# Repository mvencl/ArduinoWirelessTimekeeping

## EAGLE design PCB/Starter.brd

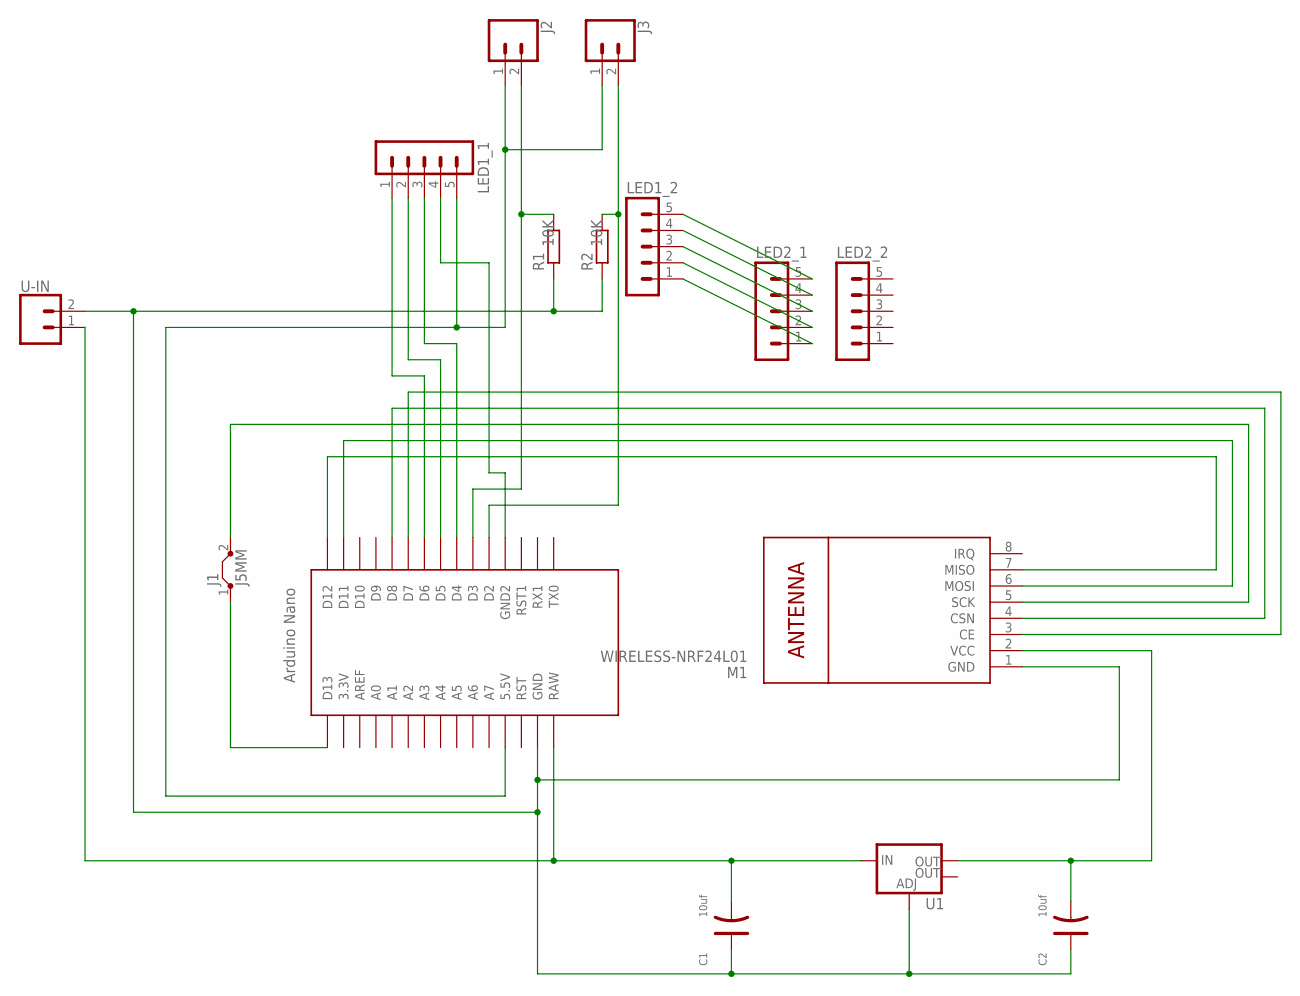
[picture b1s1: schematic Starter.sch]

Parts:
C1, C2: 10uf; AVX-B
J1: J5MM; 05
J2, J3: CONN_025MM; SCREWTERMINAL-5MM-2
LED1_1, LED1_2, LED2_1, LED2_2: MA05-1
M1: WIRELESS-NRF24L01
R1, R2: R-EU_0207/12; 0207/12
U1: V_REG_LM1117SOT223; SOT223
U$1: NANO
U-IN: CONN_025MM; SCREWTERMINAL-5MM-2

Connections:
unnamed: M1.4 (CSN), U$1.D8
unnamed: C1.+, C2.+, M1.1 (GND), R1.1, R2.1, U1.1 (ADJ), U$1.GND, U-IN.2
unnamed: C2.-, M1.2 (VCC), U1.2 (OUT)
unnamed: J1.2, M1.5 (SCK)
unnamed: LED1_2.5, LED2_1.5
unnamed: LED1_2.4, LED2_1.4
unnamed: LED1_2.3, LED2_1.3
unnamed: LED1_2.2, LED2_1.2
unnamed: LED1_2.1, LED2_1.1
unnamed: J2.1, J3.1, LED1_1.5, U$1.5V (5.5V)
unnamed: C1.-, U1.3 (IN), U$1.RAW, U-IN.1
unnamed: LED1_1.3, U$1.D4
unnamed: LED1_1.2, U$1.D5
unnamed: LED1_1.1, U$1.D6
unnamed: M1.3 (CE), U$1.D7
unnamed: M1.6 (MOSI), U$1.D11
unnamed: M1.7 (MISO), U$1.D12
unnamed: J2.2, R1.2, U$1.D3
unnamed: J3.2, R2.2, U$1.D2
unnamed: LED1_1.4, U$1.GND1 (GND2)
unnamed: J1.1, U$1.D13

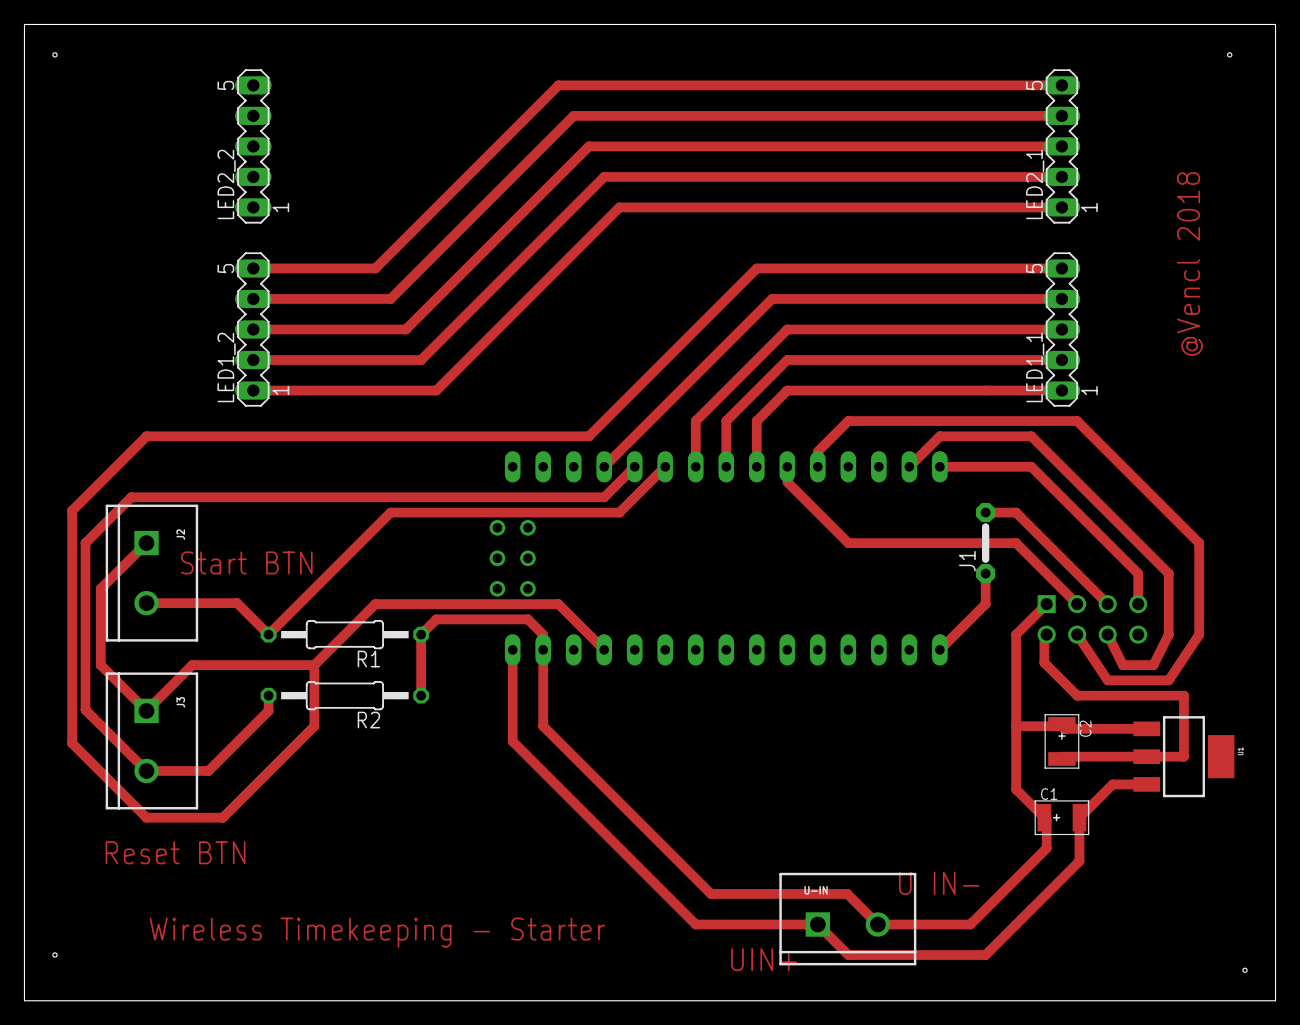
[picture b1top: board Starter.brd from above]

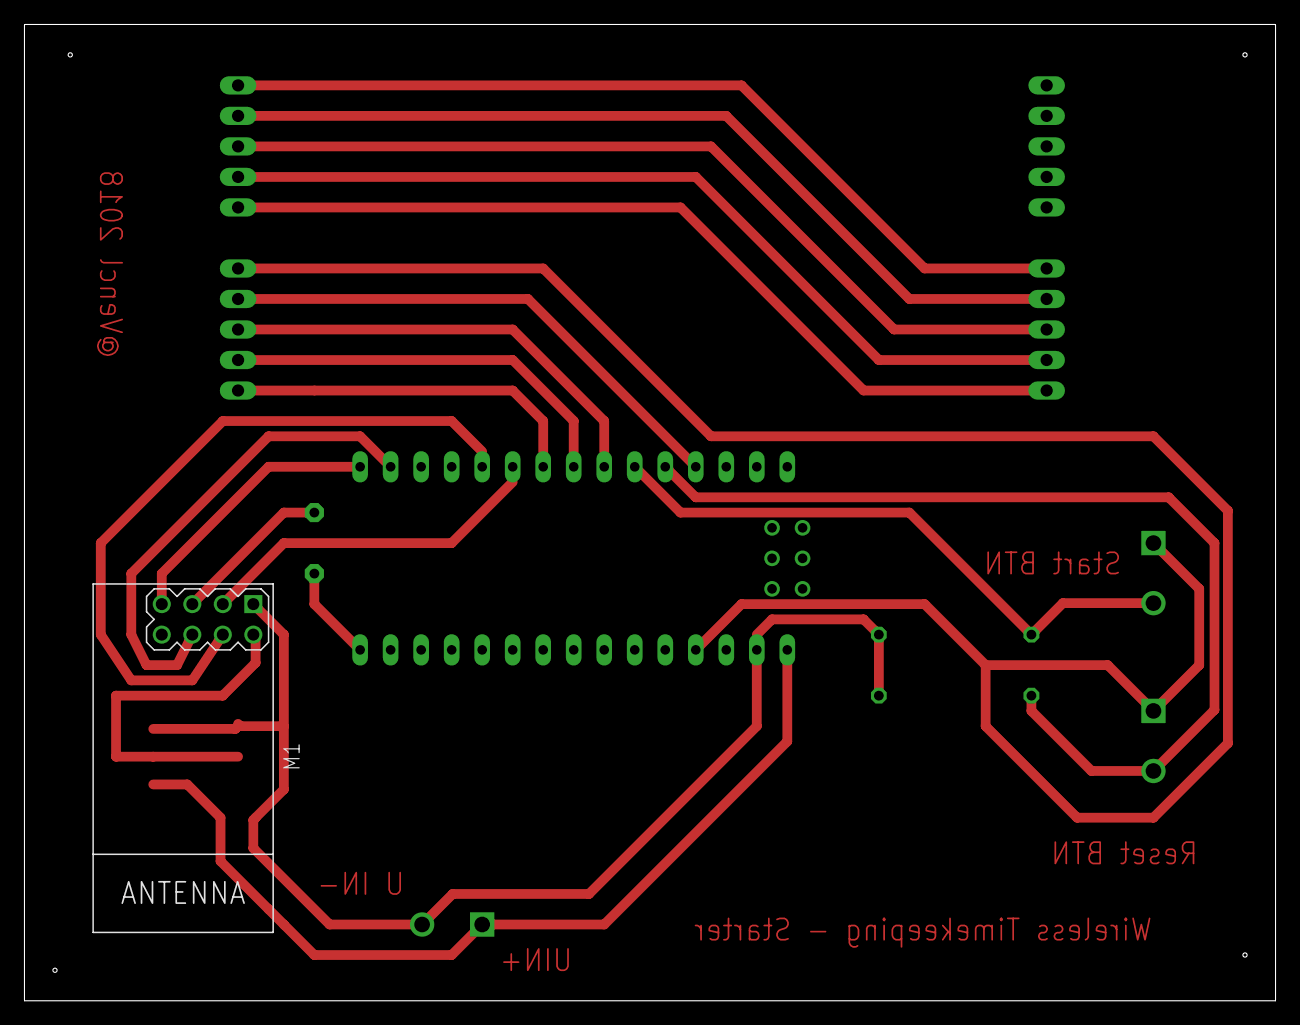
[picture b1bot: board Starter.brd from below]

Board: 2 copper layers, 104.1 x 81.3 mm, 15 parts (2 on the bottom side), 21 nets.

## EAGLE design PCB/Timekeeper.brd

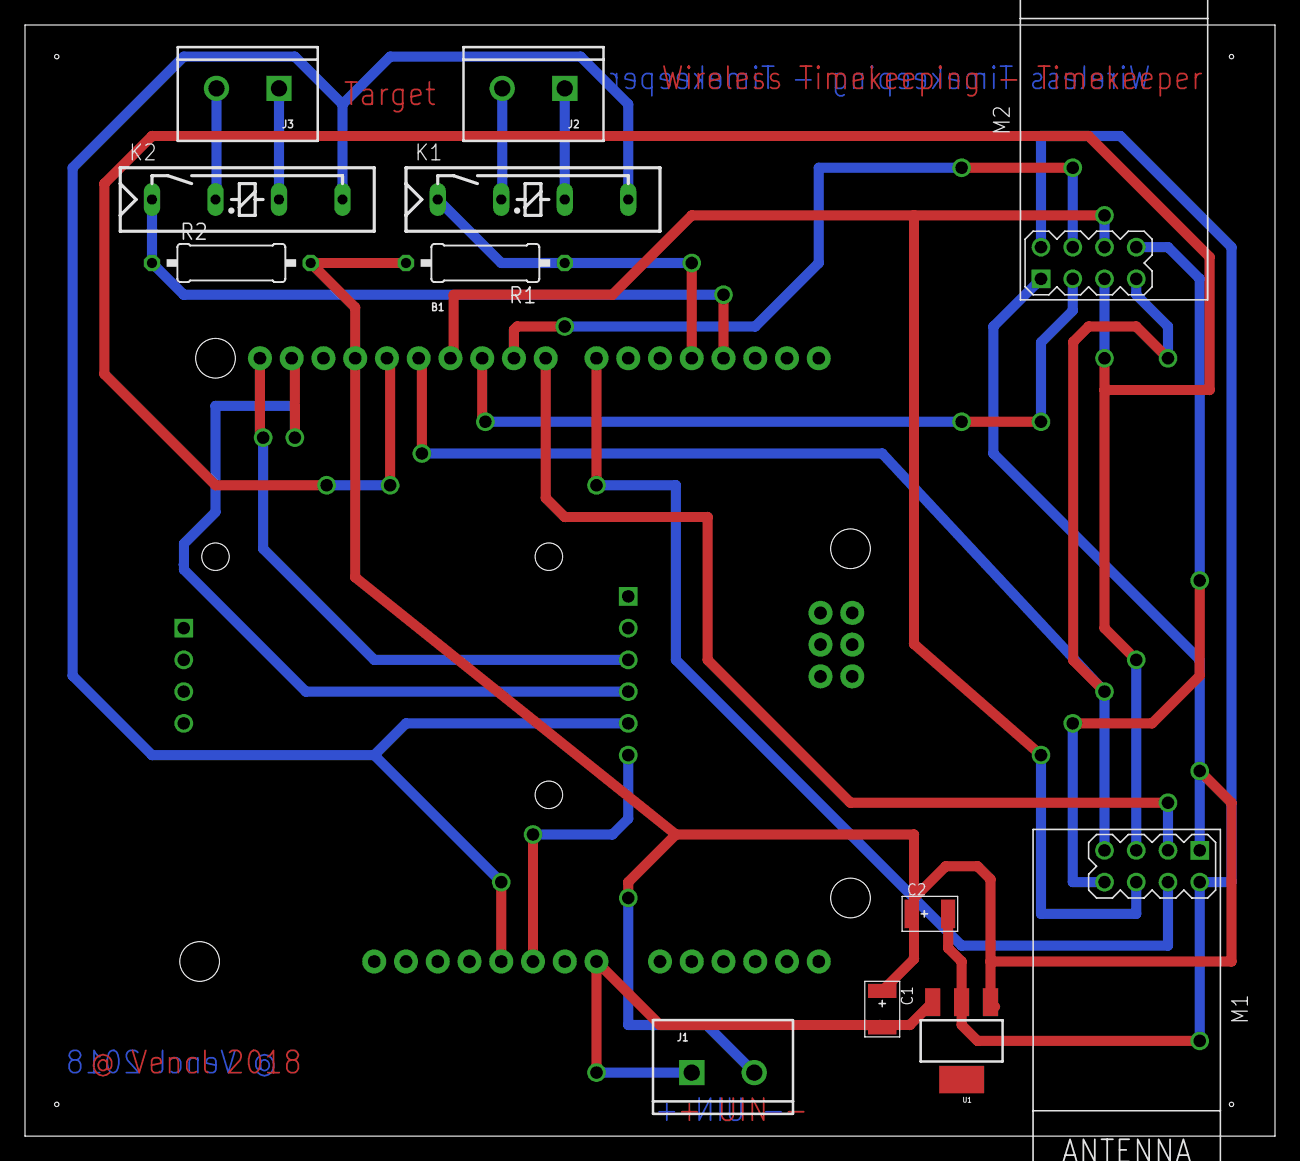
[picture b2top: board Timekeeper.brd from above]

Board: 2 copper layers, 100.0 x 88.9 mm, 14 parts (1 on the bottom side), 21 nets.

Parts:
B1: ARDUINO_UNO_R3; ARDUINO_R3
C1, C2: 10uf; AVX-B
J1, J2, J3: SCREWTERMINAL-5MM-2
K1, K2: 35701331; REED
M1, M2: WIRELESS-NRF24L01
R1, R2: 0309/12
U1: SOT223
U$2: RTC-DS3231-AT24C32

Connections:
unnamed: B1.D8, M1.3
unnamed: B1.5V, K1.7, K2.7, U$2.J1.5
unnamed: B1.D13, M1.5, M2.5
unnamed: B1.D11, M1.6, M2.6
unnamed: B1.D12, M1.7, M2.7
unnamed: M1.8, M2.8
unnamed: B1.D7, M1.4
unnamed: B1.VIN, C1.-, J1.1, U1.3
unnamed: B1.GND@1, U$2.J1.6
unnamed: B1.D4, K1.1, R1.1
unnamed: B1.SDA, U$2.J1.4
unnamed: B1.SCL, U$2.J1.3
unnamed: B1.D3, K2.1, R2.1
unnamed: B1.D10, M2.3
unnamed: J2.2, K1.3
unnamed: J2.1, K1.5
unnamed: J3.2, K2.3
unnamed: J3.1, K2.5
unnamed: B1.D9, M2.4
unnamed: B1.GND@3, C1.+, C2.+, J1.2, M1.1, M2.1, R1.2, R2.2, U1.1
unnamed: C2.-, M1.2, M2.2, U1.2

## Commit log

2018-04-25 Init working bat not in real

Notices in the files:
parts and their libraries:
SparkFun-Connectors: Licensing: Creative Commons ShareAlike 4.0 International - https://creativecommons.org/licenses/by-sa/4.0
diy-modules: Released under the Creative Commons Attribution 4.0 International License: http://creativecommons.org/licenses/by/4.0
